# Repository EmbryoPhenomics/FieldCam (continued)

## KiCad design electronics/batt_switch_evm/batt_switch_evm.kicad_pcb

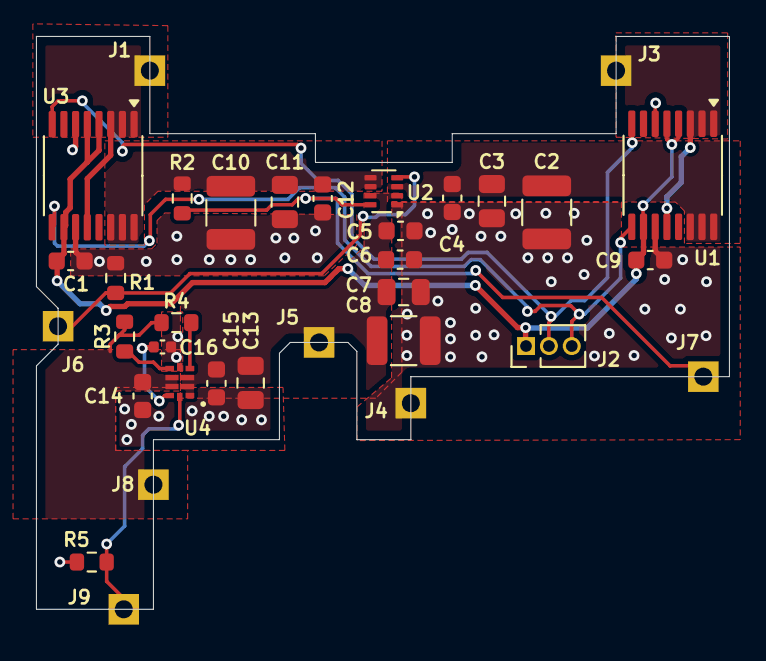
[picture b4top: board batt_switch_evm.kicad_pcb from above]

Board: 2 copper layers, 38.5 x 31.8 mm, 34 parts (0 on the bottom side), 16 nets.

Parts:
C1, C4, C5, C9, C12, C14, C15: 0.1uF; C_0603_1608Metric
C2, C8, C10: 100uF; C_1210_3225Metric
C3, C7, C11: 10uF; C_0805_2012Metric
C6: 1uF; C_0603_1608Metric
C13: 1uF; C_0805_2012Metric
C16: 1000pF; C_0402_1005Metric
J1, J3, J4, J5, J6, J7, J8, J9: Conn_01x01_Pin; PinSocket_1x01_P2.54mm_Vertical
J2: Conn_01x03_Socket; PinHeader_1x03_P1.27mm_Vertical
R1, R2, R3, R4, R5: 10kR; R_0603_1608Metric
U1, U3: INA260; TSSOP-16_4.4x5mm_P0.65mm
U2: TPS2117; SOT-583-8
U4: TPS22997RYZR; WQFN-HR10_RYZ_TEX

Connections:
5V_EN: J9.1, R5.2, U4.10 (ON)
+3.3V: C1.1, C9.1, J2.1, U1.4 (A1), U1.5 (A0), U1.10 (VS), U3.4 (A1), U3.5 (A0), U3.10 (VS)
+5V_IN: C14.1, J8.1, R3.1, R4.1, U4.7 (VOUT), U4.8 (VOUT)
+BATT1: C10.1, C11.1, C12.1, R2.2, U2.5 (MODE), U2.6 (VIN2), U3.14 (IN-), U3.15 (IN-), U3.16 (IN-)
+BATT2: C2.1, C3.1, C4.1, U1.14 (IN-), U1.15 (IN-), U1.16 (IN-), U2.3 (VIN1)
+VBAT: C5.1, C6.1, C7.1, C8.1, C13.1, C15.1, J5.1, U2.2 (VOUT), U2.7 (VOUT), U4.1 (VBIAS), U4.2 (VIN), U4.3 (VIN)
BATT1_IN: J1.1, U3.1 (IN+), U3.2 (IN+), U3.3 (IN+), U3.12 (VBUS)
BATT2_IN: J3.1, U1.1 (IN+), U1.2 (IN+), U1.3 (IN+), U1.12 (VBUS)
BATT_ST: J7.1, R2.1, U2.8 (ST)
BATT_SW: J6.1, R1.1, U2.4 (PR1)
GND: C1.2, C2.2, C3.2, C4.2, C5.2, C6.2, C7.2, C8.2, C9.2, C10.2, C11.2, C12.2, C13.2, C14.2, C15.2, C16.2, J4.1, R1.2, R5.1, U1.6 (GND), U1.11 (GND), U2.1 (GND), U3.6 (GND), U3.11 (GND), U4.5 (GND)
MSCL: J2.3, U1.9 (SCL), U3.9 (SCL)
MSDA: J2.2, U1.8 (SDA), U3.8 (SDA)
unnamed: C16.1, U4.9 (CT)
unnamed: R4.2, U4.4 (PG)
unnamed: R3.2, U4.6 (QOD)

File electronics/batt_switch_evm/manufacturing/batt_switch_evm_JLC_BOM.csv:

Comment,Designator,Footprint,JLCPCB Part #,Notes,Correct?
INA260,"U3,U1",TSSOP-16_4.4x5mm_P0.65mm,C2155885,,
10kR,"R3,R5,R4,R2,R1",R_0603_1608Metric,C99198,,
1uF,C6,C_0603_1608Metric,C77386,,
0.1uF,"C4,C1,C9,C15,C12,C14,C5",C_0603_1608Metric,C77055,,
100uF,"C10,C8,C2",C_1210_3225Metric,C5719639,,
10uF,"C7,C3,C11",C_0805_2012Metric,C84416,,
1000pF,C16,C_0402_1005Metric,C76947,,
TPS22997RYZR,U4,WQFN-HR10_RYZ_TEX,C17286840,,
1uF,C13,C_0805_2012Metric,C77083,,
TPS2117,U2,SOT-583-8,C22399676,,

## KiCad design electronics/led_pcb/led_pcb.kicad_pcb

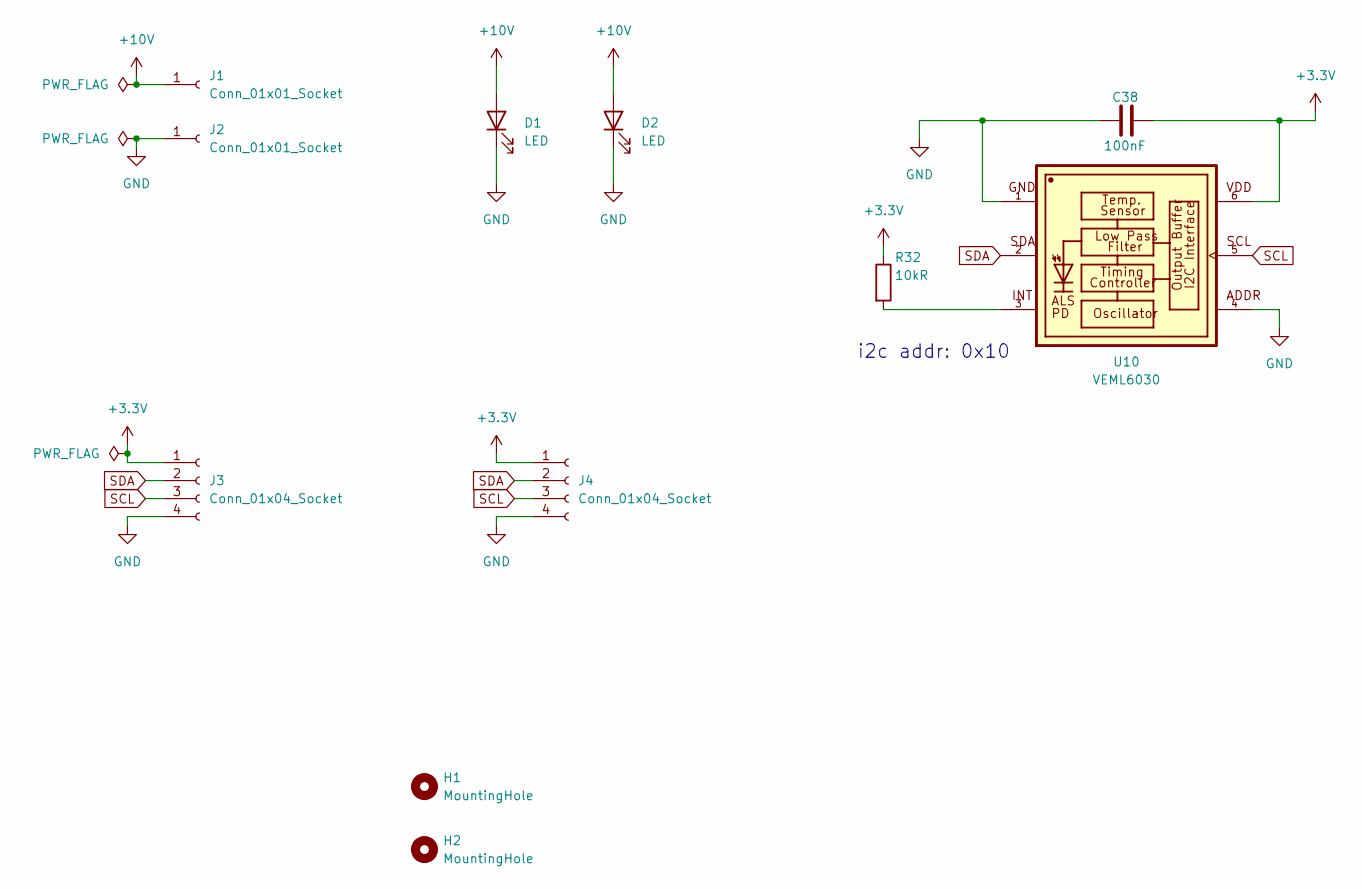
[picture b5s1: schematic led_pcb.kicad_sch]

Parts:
C38: 100nF; C_0402_1005Metric
D1, D2: LED; LED-SMD_L3.5-W2.8-R-FD-WHITE
H1, H2: MountingHole; MountingHole_2.2mm_M2
J1, J2: Conn_01x01_Socket; TestPoint_THTPad_2.0x2.0mm_Drill1.0mm
J3, J4: Conn_01x04_Socket; PinHeader_1x04_P1.27mm_Vertical
R32: 10kR; R_0402_1005Metric
U10: VEML6030; VISHAY_VEML6030_2X2X0.87

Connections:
+3.3V: C38.2, J3.1, J4.1, R32.1, U10.6
+10V: D1.2 (A), D2.2 (A), J1.1
GND: C38.1, D1.1 (K), D2.1 (K), J2.1, J3.4, J4.4, U10.1, U10.4
MSCL: J3.3, J4.3, U10.5
MSDA: J3.2, J4.2, U10.2
unnamed: R32.2, U10.3

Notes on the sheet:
i2c addr: 0x10

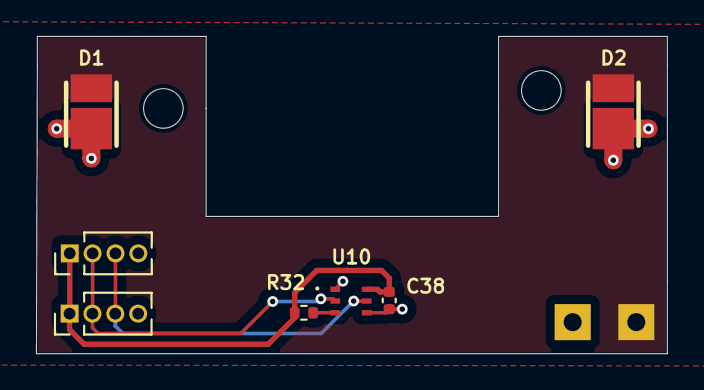
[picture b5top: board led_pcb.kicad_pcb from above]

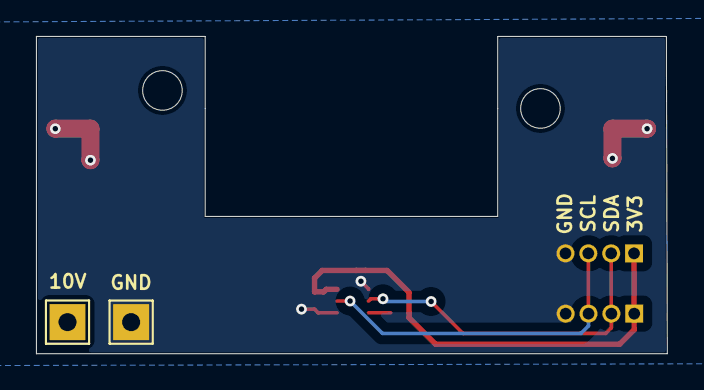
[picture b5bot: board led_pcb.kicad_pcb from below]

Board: 2 copper layers, 35.1 x 17.6 mm, 11 parts (2 on the bottom side), 6 nets.

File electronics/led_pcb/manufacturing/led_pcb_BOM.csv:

"Reference","Qty","Value","DNP","Exclude from BOM","Exclude from Board","Footprint","Datasheet"
"C38","1","100nF","","","","Capacitor_SMD:C_0402_1005Metric","~"
"D1,D2","2","LED","","","","jlcpcb:LED-SMD_L3.5-W2.8-R-FD-WHITE","~"
"H1,H2","2","MountingHole","","Excluded from BOM","","MountingHole:MountingHole_2.2mm_M2","~"
"J1,J2","2","Conn_01x01_Socket","","","","TestPoint:TestPoint_THTPad_2.0x2.0mm_Drill1.0mm","~"
"J3,J4","2","Conn_01x04_Socket","","","","Connector_PinHeader_1.27mm:PinHeader_1x04_P1.27mm_Vertical","~"
"R32","1","10kR","","","","Resistor_SMD:R_0402_1005Metric","~"
"U10","1","VEML6030","","","","jlcpcb:VISHAY_VEML6030_2X2X0.87",""

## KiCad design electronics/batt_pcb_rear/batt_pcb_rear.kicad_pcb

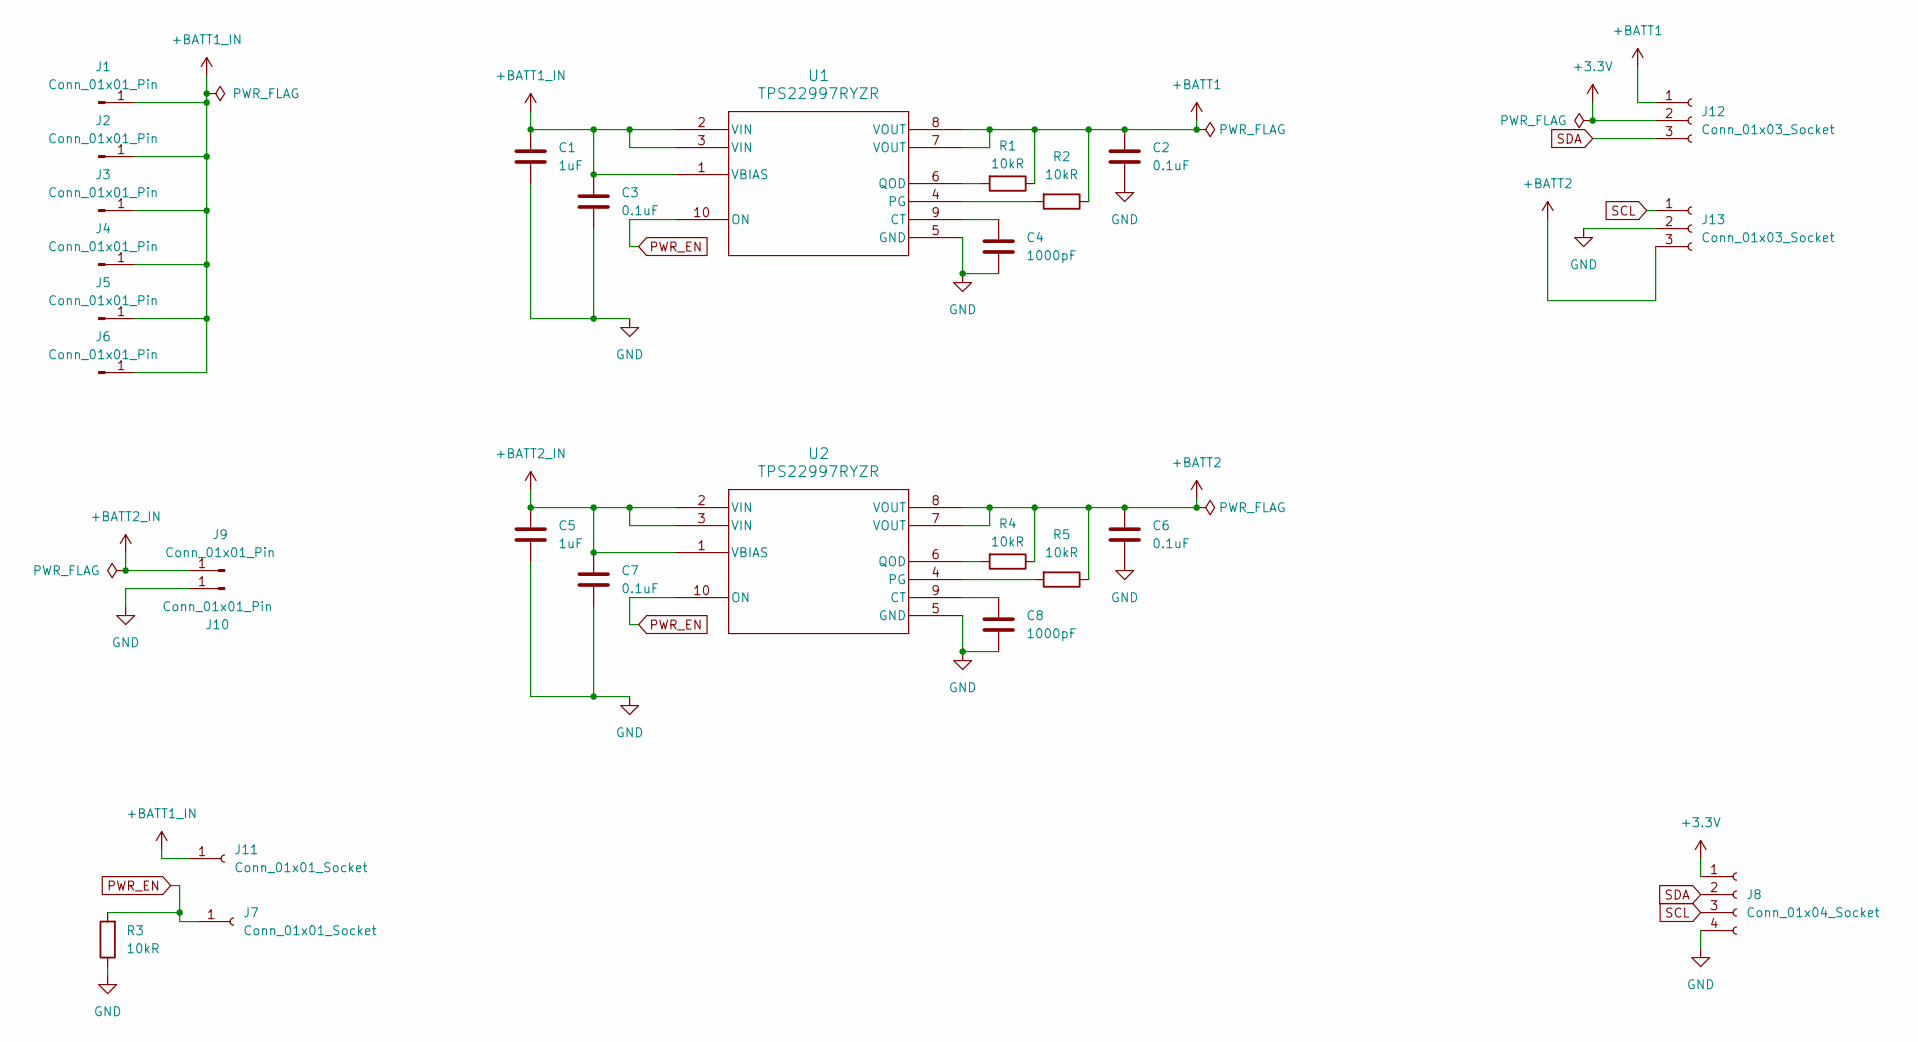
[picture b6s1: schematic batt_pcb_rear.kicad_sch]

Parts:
C1, C5: 1uF; C_0805_2012Metric
C2, C3, C6, C7: 0.1uF; C_0603_1608Metric
C4, C8: 1000pF; C_0402_1005Metric
J1, J2, J3, J4, J5, J6: Conn_01x01_Pin; TestPoint_Pad_D2.5mm
J7, J11: Conn_01x01_Socket; SolderWire-1sqmm_1x01_D1.4mm_OD2.7mm
J8: Conn_01x04_Socket; JST_SH_BM04B-SRSS-TB_1x04-1MP_P1.00mm_Vertical
J9, J10: Conn_01x01_Pin; TestPoint_THTPad_4.0x4.0mm_Drill2.0mm
J12, J13: Conn_01x03_Socket; 16128981
R1, R2, R3, R4, R5: 10kR; R_0603_1608Metric
U1, U2: TPS22997RYZR; WQFN-HR10_RYZ_TEX

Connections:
+3.3V: J8.1, J12.2
+BATT1: C2.1, J12.1, R1.1, R2.1, U1.7 (VOUT), U1.8 (VOUT)
+BATT1_IN: C1.1, C3.1, J1.1, J2.1, J3.1, J4.1, J5.1, J6.1, J11.1, U1.1 (VBIAS), U1.2 (VIN), U1.3 (VIN)
+BATT2: C6.1, J13.3, R4.1, R5.1, U2.7 (VOUT), U2.8 (VOUT)
+BATT2_IN: C5.1, C7.1, J9.1, U2.1 (VBIAS), U2.2 (VIN), U2.3 (VIN)
GND: C1.2, C2.2, C3.2, C4.2, C5.2, C6.2, C7.2, C8.2, J8.4, J10.1, J13.2, R3.1, U1.5 (GND), U2.5 (GND)
unnamed: C4.1, U1.9 (CT)
unnamed: R2.2, U1.4 (PG)
unnamed: R1.2, U1.6 (QOD)
unnamed: C8.1, U2.9 (CT)
unnamed: R5.2, U2.4 (PG)
unnamed: R4.2, U2.6 (QOD)
PWR_EN: J7.1, R3.2, U1.10 (ON), U2.10 (ON)
SCL: J8.3, J13.1
SDA: J8.2, J12.3

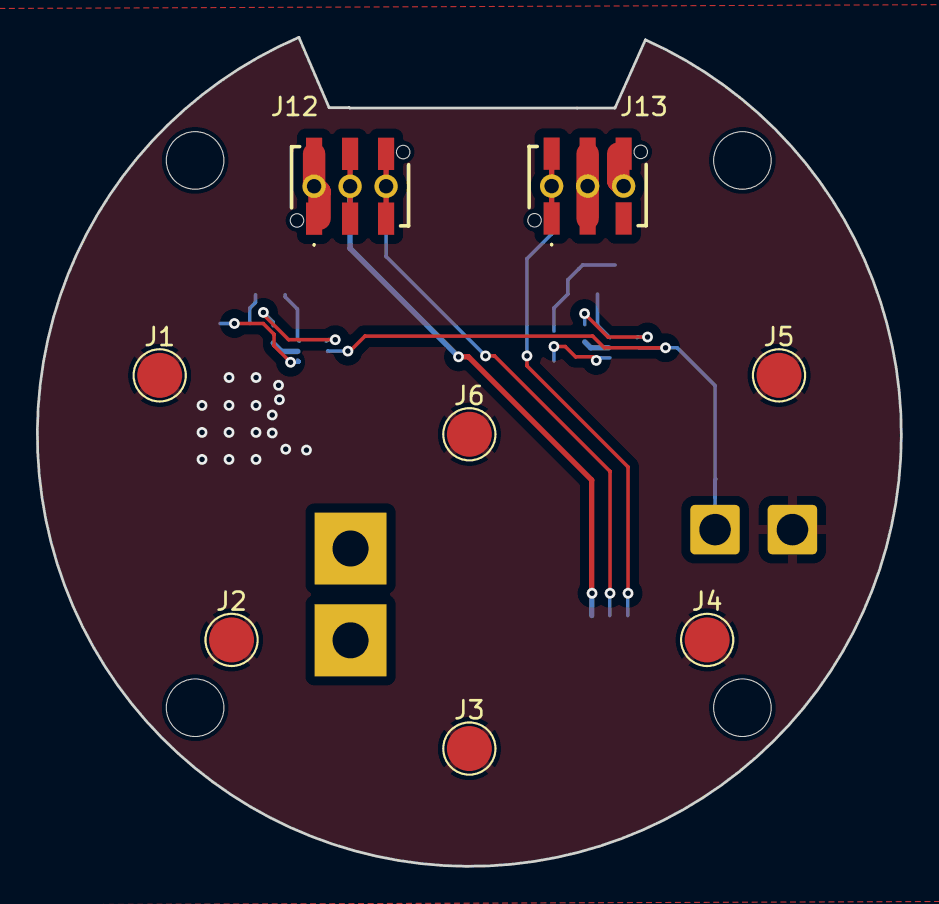
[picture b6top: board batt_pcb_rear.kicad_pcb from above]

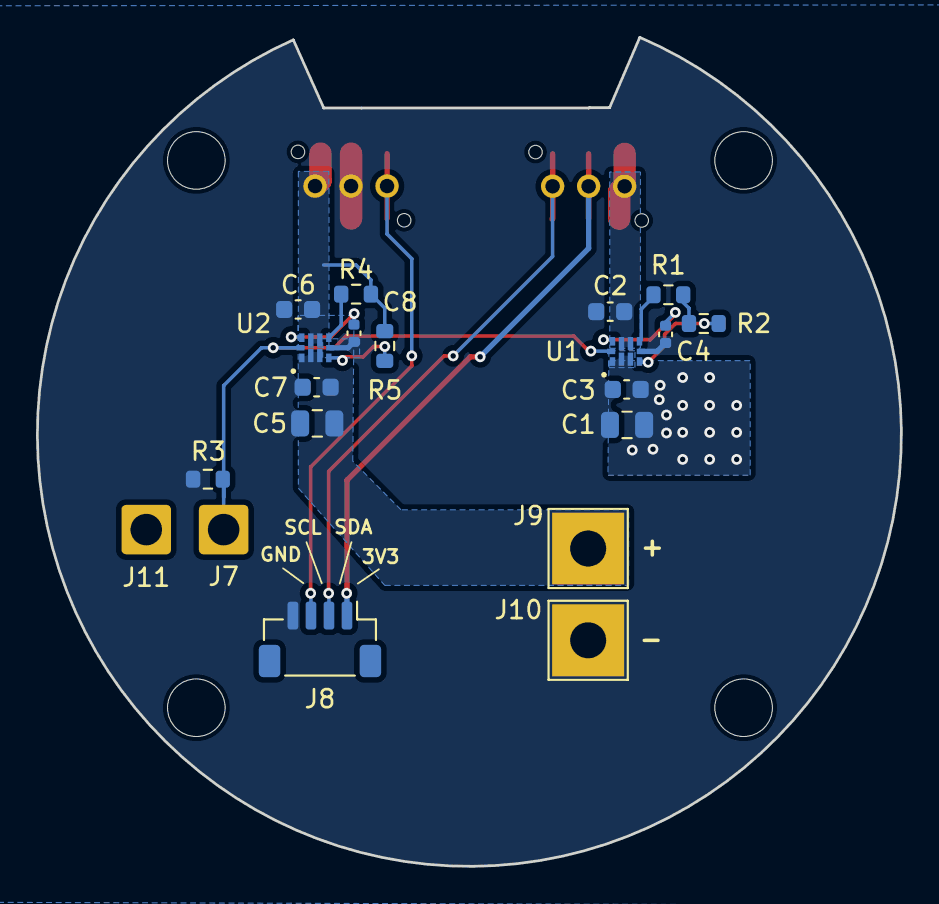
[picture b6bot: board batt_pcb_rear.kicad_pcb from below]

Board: 2 copper layers, 48.0 x 46.1 mm, 32 parts (20 on the bottom side), 15 nets.

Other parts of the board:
UNK_HOLE_0: dummyfp0
UNK_HOLE_1: dummyfp1
UNK_HOLE_2: dummyfp2
UNK_HOLE_3: dummyfp3

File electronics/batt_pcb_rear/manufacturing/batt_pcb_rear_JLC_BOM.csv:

Comment,Designator,Footprint,JLCPCB Part #,Notes,Correct?
1uF,"C1,C5",Capacitor_SMD:C_0805_2012Metric,C77083,,
0.1uF,"C2,C3,C6,C7",Capacitor_SMD:C_0603_1608Metric,C77055,,
1000pF,"C4,C8",Capacitor_SMD:C_0402_1005Metric,C76947,,
10kR,"R1,R2,R3,R4,R5",Resistor_SMD:R_0603_1608Metric,C99198,,
TPS22997RYZR,"U1,U2",jlcpcb:WQFN-HR10_RYZ_TEX,C17286840,,
Conn_01x04_Socket,J8,Connector_JST:JST_SH_BM04B-SRSS-TB_1x04-1MP_P1.00mm_Vertical,C160390,,

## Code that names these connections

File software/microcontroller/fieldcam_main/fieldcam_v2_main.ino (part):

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// Dynamic lighting based on light sensor

// Blinky
#define LED_BUILTIN PA0

// Pin Definitions:
#define SDA1_MASTER PA10
#define SCL1_MASTER PA9

#define SDA2_SLAVE PB11 // Slave to RPi Master
#define SCL2_SLAVE PB10 // Slave to RPi Master

// SD chip select
#define SD_CS PA5

/* Power Control */
#define EN_5V PB13
#define EN_10V PB14
#define BATT_SW PA8
#define BATT_ST PB15

// Battery LEDs
#define BATT1_LED PB5
#define BATT2_LED PB6

// Mode Switches
#define TURN_ON_OFF PB2

#define RPI_GPIO22 PB12

// Definitions of global variables -----
float rpi_volts, rpi_current, rpi_power;
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    /*  INPUTS
    --------------*/ 
    pinMode(TURN_ON_OFF, INPUT);
    pinMode(RPI_GPIO22, INPUT);
    pinMode(BATT_ST, INPUT);

    /*  OUTPUTS
    --------------*/ 
    pinMode(LED_BUILTIN, OUTPUT);digitalWrite(LED_BUILTIN, LOW);  // Led Pin
    pinMode(BATT1_LED, OUTPUT);digitalWrite(BATT1_LED, LOW);  // BATT1 Led Pin
    pinMode(BATT2_LED, OUTPUT);digitalWrite(BATT2_LED, LOW);  // BATT2 Led Pin

    pinMode(EN_5V, OUTPUT);digitalWrite(EN_5V, LOW);  // System Power off
    pinMode(EN_10V, OUTPUT);digitalWrite(EN_10V, LOW);  // LED 14V boost off
    pinMode(BATT_SW, OUTPUT);digitalWrite(BATT_SW, LOW); // BATT1 = low, BATT2 = high

}
// ---------------------------------------------------------------------------------------
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
  // Somewhat janky periodic check to turn on/off external LEDs
  // Would be better as an interrupt
  if (digitalRead(RPI_GPIO22) == HIGH) {
    lights_on(led_brightness);  
  } else {
    lights_off();
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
